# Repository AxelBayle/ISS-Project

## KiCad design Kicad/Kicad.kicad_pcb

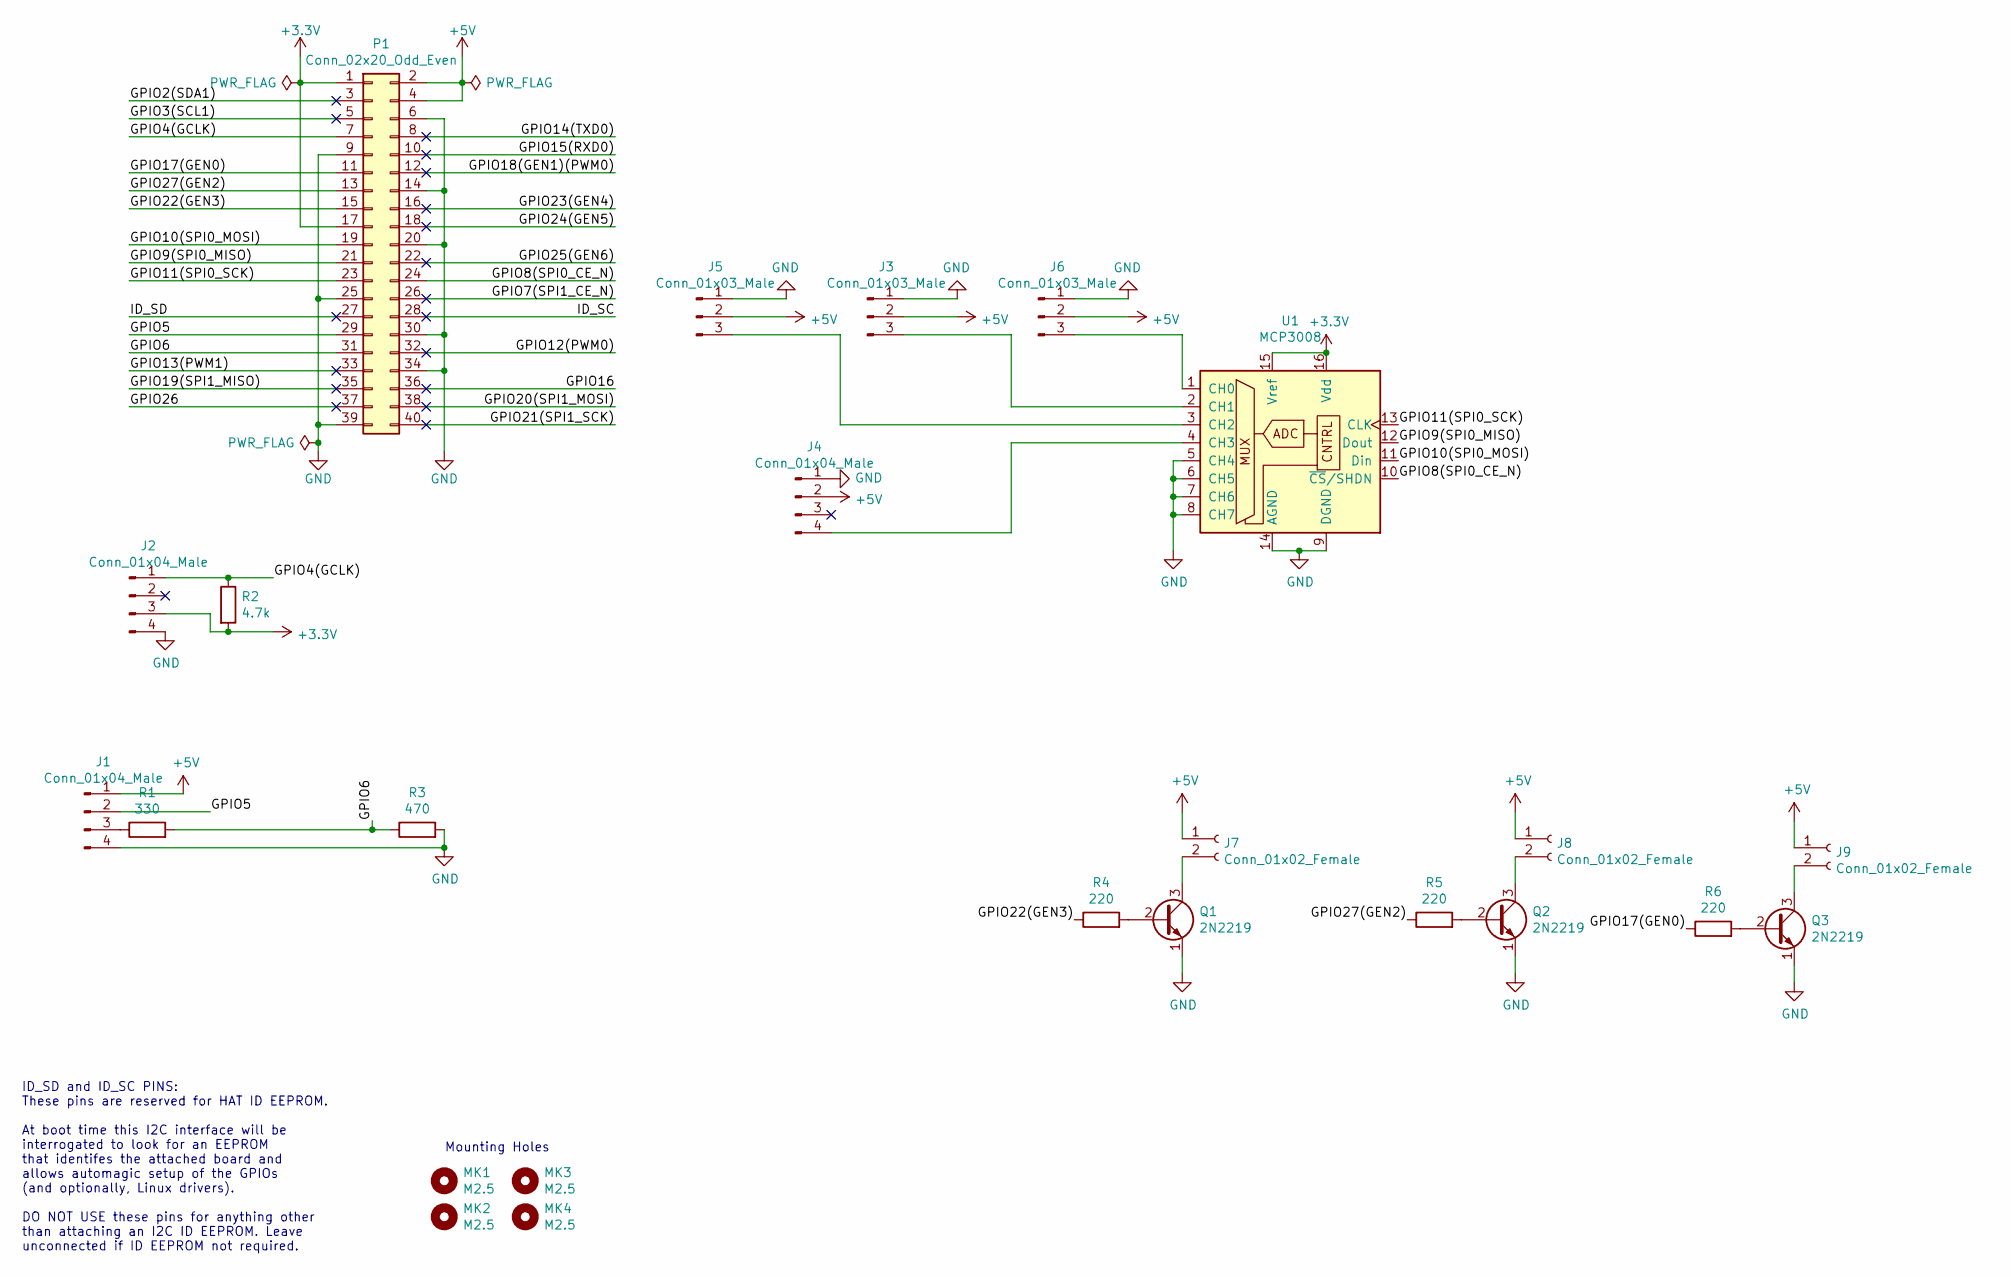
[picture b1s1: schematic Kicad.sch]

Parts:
J1: Conn_01x04_Male; PinHeader_1x04_P2.54mm_Vertical
J2, J4: Conn_01x04_Male; NS-Tech_Grove_1x04_P2mm_Vertical
J3, J5, J6: Conn_01x03_Male; PinHeader_1x03_P2.54mm_Vertical
J7, J8, J9: Conn_01x02_Female; PinSocket_1x02_P2.54mm_Vertical
MK1, MK2, MK3, MK4: M2.5; MountingHole_2.7mm_M2.5
P1: Conn_02x20_Odd_Even; PinSocket_2x20_P2.54mm_Vertical
Q1, Q2, Q3: 2N2219; TO-39-3
R1: 330; R_Axial_DIN0207_L6.3mm_D2.5mm_P10.16mm_Horizontal
R2: 4.7k; R_Axial_DIN0207_L6.3mm_D2.5mm_P10.16mm_Horizontal
R3: 470; R_Axial_DIN0207_L6.3mm_D2.5mm_P10.16mm_Horizontal
R4, R5, R6: 220; R_Axial_DIN0207_L6.3mm_D2.5mm_P10.16mm_Horizontal
U1: MCP3008; DIP-16_W10.16mm_LongPads

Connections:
+3V3: J2.3, P1.1, P1.17, R2.2, U1.15 (Vref), U1.16 (Vdd)
+5V: J1.1, J3.2, J4.2, J5.2, J6.2, J7.1, J8.1, J9.1, P1.2, P1.4
/GPIO2(SDA1): P1.3
/GPIO3(SCL1): P1.5
/GPIO4(GCLK): J2.1, P1.7, R2.1
/GPIO5: J1.2, P1.29
/GPIO6: P1.31, R1.2, R3.1
/GPIO7(SPI1_CE_N): P1.26
/GPIO8(SPI0_CE_N): P1.24, U1.10 (~CS~/SHDN)
/GPIO9(SPI0_MISO): P1.21, U1.12 (Dout)
/GPIO10(SPI0_MOSI): P1.19, U1.11 (Din)
/GPIO11(SPI0_SCK): P1.23, U1.13 (CLK)
/GPIO12(PWM0): P1.32
/GPIO13(PWM1): P1.33
/GPIO14(TXD0): P1.8
/GPIO15(RXD0): P1.10
/GPIO16: P1.36
/GPIO17(GEN0): P1.11, R6.1
/GPIO18(GEN1)(PWM0): P1.12
/GPIO19(SPI1_MISO): P1.35
/GPIO20(SPI1_MOSI): P1.38
/GPIO21(SPI1_SCK): P1.40
/GPIO22(GEN3): P1.15, R4.1
/GPIO23(GEN4): P1.16
/GPIO24(GEN5): P1.18
/GPIO25(GEN6): P1.22
/GPIO26: P1.37
/GPIO27(GEN2): P1.13, R5.1
/ID_SC: P1.28
/ID_SD: P1.27
GND: J1.4, J2.4, J3.1, J4.1, J5.1, J6.1, P1.6, P1.9, P1.14, P1.20, P1.25, P1.30, P1.34, P1.39, Q1.1 (E), Q2.1 (E), Q3.1 (E), R3.2, U1.5 (CH4), U1.6 (CH5), U1.7 (CH6), U1.8 (CH7), U1.9 (DGND), U1.14 (AGND)
unnamed: J1.3, R1.1
unnamed: J3.3, U1.2 (CH1)
unnamed: J4.4, U1.4 (CH3)
unnamed: J5.3, U1.3 (CH2)
unnamed: J6.3, U1.1 (CH0)
unnamed: J7.2, Q1.3 (C)
unnamed: J8.2, Q2.3 (C)
unnamed: J9.2, Q3.3 (C)
unnamed: Q1.2 (B), R4.2
unnamed: Q2.2 (B), R5.2
unnamed: Q3.2 (B), R6.2

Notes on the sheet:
ID_SD and ID_SC PINS: These pins are reserved for HAT ID EEPROM. At boot time this I2C interface will be interrogated to look for an EEPROM that identifes the attached board and allows automagic setup of the GPIOs (and optionally, Linux drivers). DO NOT USE these pins for anything other than attach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
Mounting Holes

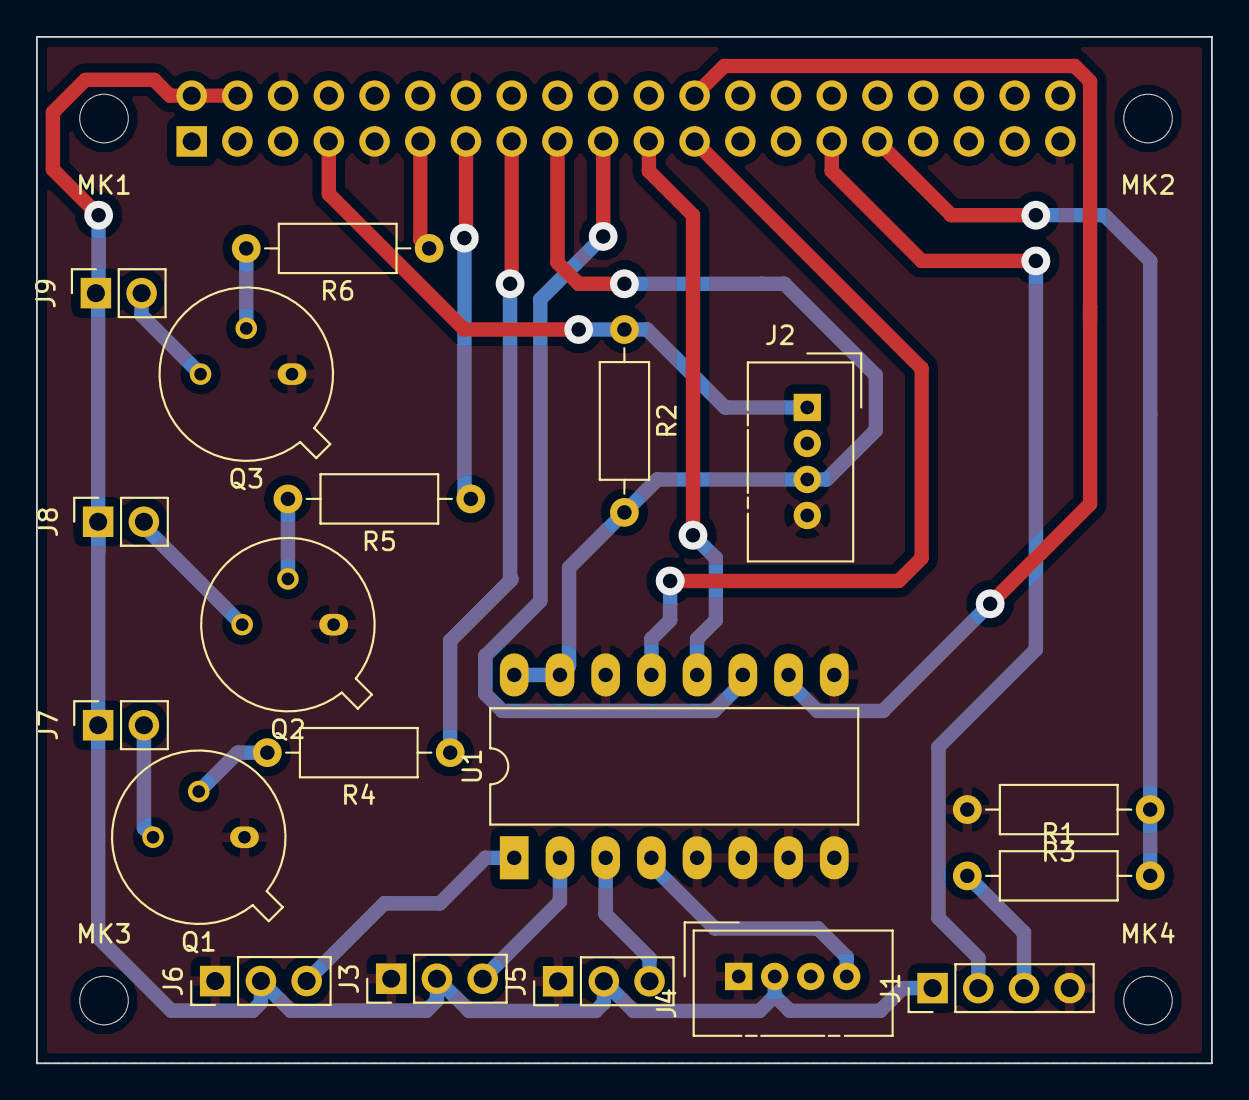
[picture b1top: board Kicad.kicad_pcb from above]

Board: 2 copper layers, 65.3 x 57.0 mm, 24 parts (1 on the bottom side), 24 nets.

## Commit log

2018-11-30 Branche dev
2018-12-01 gestion ultrasons
2018-12-01 premier commit ultrasons
2018-12-04 fonction distance
2018-12-04 correction distance
2018-12-04 creation
2018-12-05 get temperature
2018-12-12 GetACD Function
2018-12-12 Realisation du PCB
2018-12-16 Modification Kicad
2018-12-16 ajout du module server watree
2019-01-07 RATTRAPAGES git statusgit status
2019-01-09 ajout delai variable
2019-01-13 correction pin
2019-01-13 ajout file test
2019-01-13 correction light
2019-01-14 Derniere version application
2019-01-14 correctiopn pin us
2019-01-14 modif du test arrosage
2019-01-16 correction pb connexion multiples
